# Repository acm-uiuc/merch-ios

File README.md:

# Merch Point of Sale iOS App

## Getting involved

We encourage you to participate in this open source project. We love Pull Requests, ideas, code reviews or any kind of positive contribution. GitHub issues are enabled on this repository, if you spot a bug please create a new issue.

Don't know where to start? Check issues for bugs we haven't gotten around to squashing, features we still need to implement and more. The team is active on *Gitter* and we would love to answer any questions you have.

## Requirements

XCode 8

iOS 10.2 SDK

An iPad running iOS 10.0 or newer

A Groot Client Key (more on this in API)

A code signing key from Apple is required to deploy apps to a device. Without a developer key, the app can only be installed on the iPhone/iPad Simulator.

## API

The project runs on ACM@UIUC Groot services, with routes specific to Merch maintained in https://github.com/acm-uiuc/groot-merch-service.

In order to access these services you will need a client key, which you can ask for on the Groot Gitter.

## License

This project is licensed under the University of Illinois/NCSA Open Source License. For a full copy of this license take a look at the LICENSE file. 

When contributing new files to this project, preappend the following header to the file as a comment: 

```
Copyright © 2017, ACM@UIUC

This file is part of the Merch Project.  
 
The Merch Project is open source software, released under the University of Illinois/NCSA Open Source License. 
You should have received a copy of this license in a file with the distribution.
```

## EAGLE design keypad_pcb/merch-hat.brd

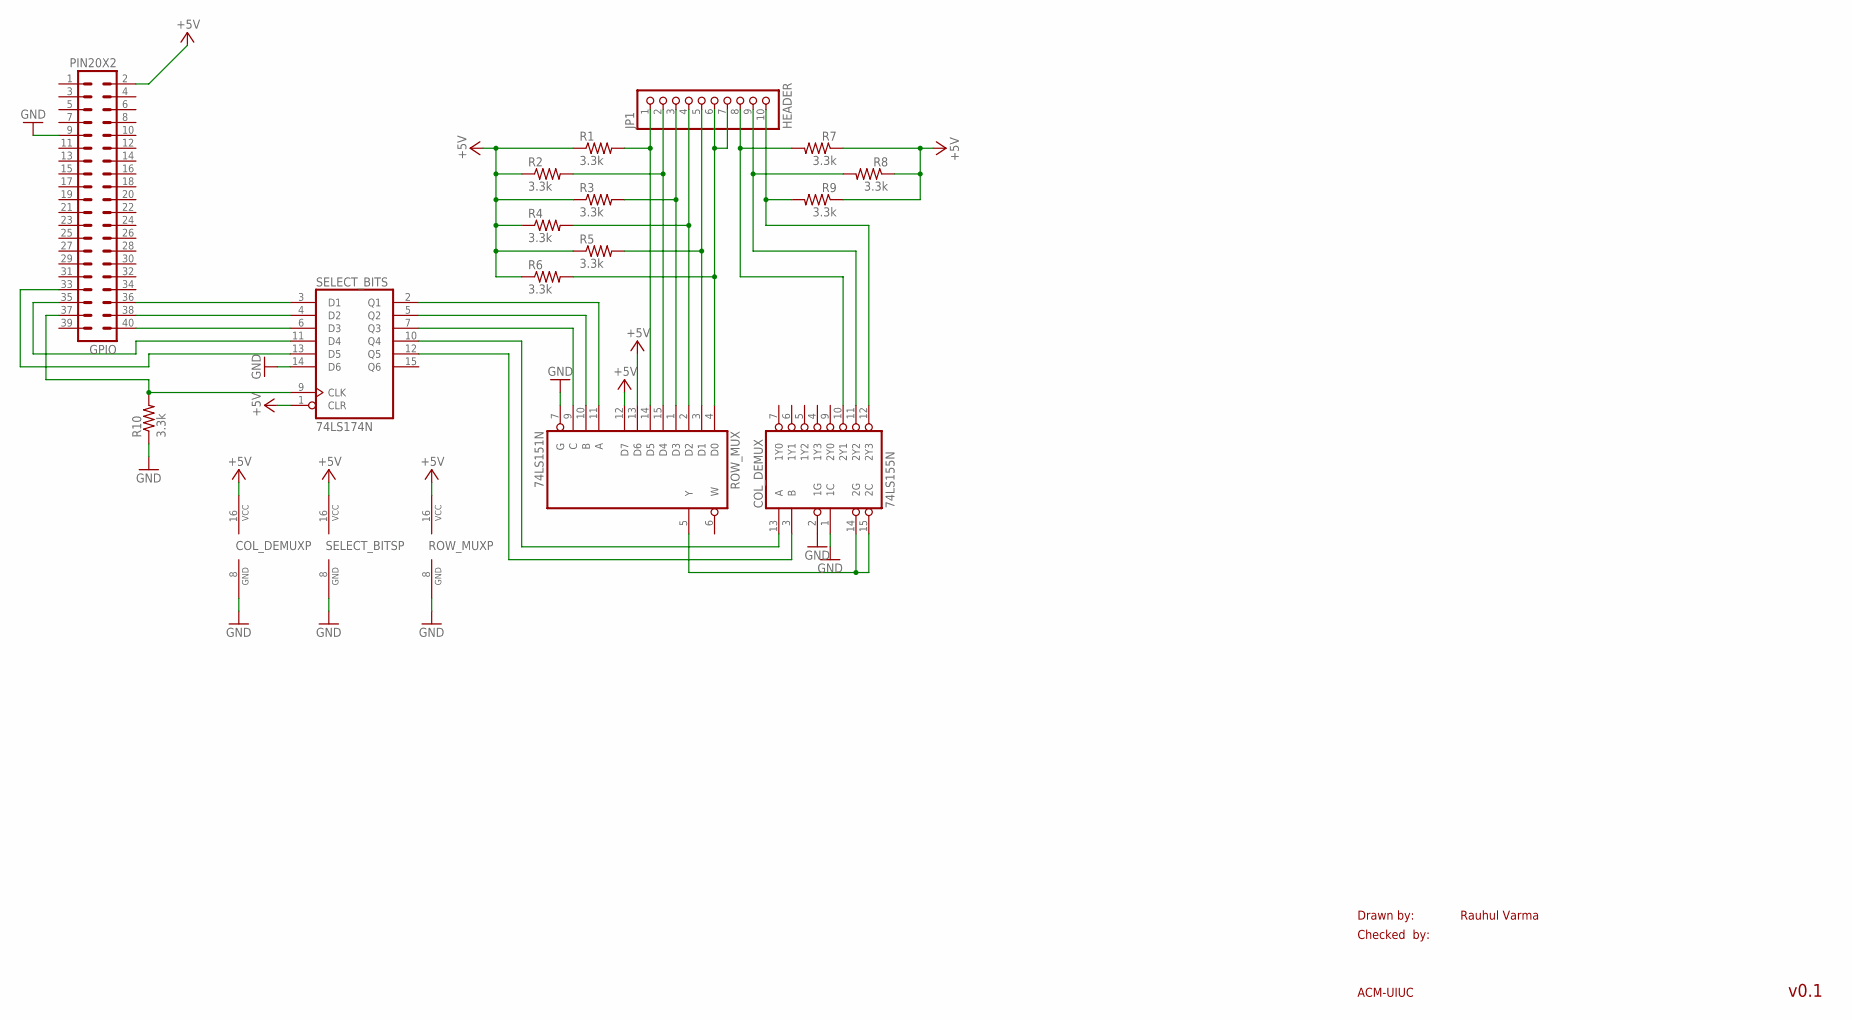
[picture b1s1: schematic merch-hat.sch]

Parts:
COL_DEMUX: 74LS155N; DIL16
GPIO: PIN20X2; PIN_20X2
JP1: HEADER; 1X10
R1, R2, R3, R4, R5, R6, R7, R8, R9, R10: 3.3k; 0207/10
ROW_MUX: 74LS151N; DIL16
SELECT_BITS: 74LS174N; DIL16

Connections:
+5V: COL_DEMUX.16 (VCC), GPIO.2, R1.1, R2.1, R3.1, R4.1, R5.1, R6.1, R7.1, R8.1, R9.1, ROW_MUX.12 (D7), ROW_MUX.13 (D6), ROW_MUX.16 (VCC), SELECT_BITS.1 (CLR), SELECT_BITS.16 (VCC)
GND: COL_DEMUX.1 (1C), COL_DEMUX.2 (1G), COL_DEMUX.8 (GND), GPIO.9, R10.1, ROW_MUX.7 (G), ROW_MUX.8 (GND), SELECT_BITS.8 (GND), SELECT_BITS.14 (D6)
unnamed: JP1.1, R1.2, ROW_MUX.14 (D5)
unnamed: GPIO.38, SELECT_BITS.4 (D2)
unnamed: GPIO.40, SELECT_BITS.6 (D3)
unnamed: JP1.2, R2.2, ROW_MUX.15 (D4)
unnamed: GPIO.35, SELECT_BITS.11 (D4)
unnamed: GPIO.36, SELECT_BITS.3 (D1)
unnamed: GPIO.33, SELECT_BITS.13 (D5)
unnamed: GPIO.37, R10.2, SELECT_BITS.9 (CLK)
unnamed: JP1.3, R3.2, ROW_MUX.1 (D3)
unnamed: JP1.4, R4.2, ROW_MUX.2 (D2)
unnamed: JP1.5, R5.2, ROW_MUX.3 (D1)
unnamed: ROW_MUX.11 (A), SELECT_BITS.2 (Q1)
unnamed: JP1.6, JP1.7, R6.2, ROW_MUX.4 (D0)
unnamed: COL_DEMUX.10 (2Y1), JP1.8, R7.2
unnamed: COL_DEMUX.11 (2Y2), JP1.9, R8.2
unnamed: COL_DEMUX.12 (2Y3), JP1.10, R9.2
unnamed: ROW_MUX.10 (B), SELECT_BITS.5 (Q2)
unnamed: ROW_MUX.9 (C), SELECT_BITS.7 (Q3)
unnamed: COL_DEMUX.13 (A), SELECT_BITS.10 (Q4)
unnamed: COL_DEMUX.3 (B), SELECT_BITS.12 (Q5)
unnamed: COL_DEMUX.14 (2G), COL_DEMUX.15 (2C), ROW_MUX.5 (Y)

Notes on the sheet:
Drawn by:
Checked by:
ACM-UIUC
Rauhul Varma
v0.1

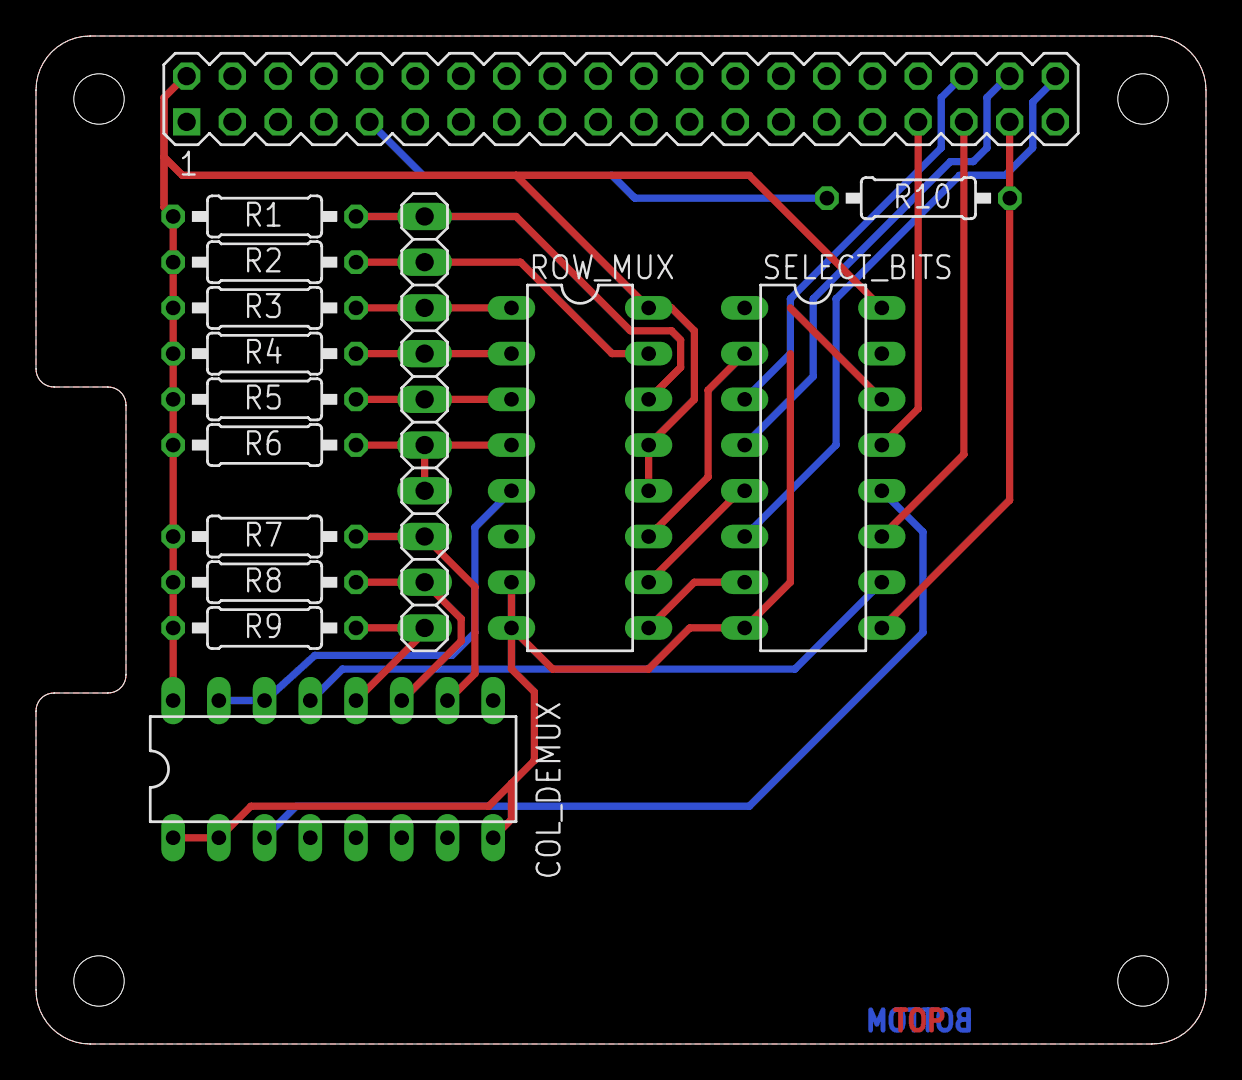
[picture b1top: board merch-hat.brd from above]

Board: 2 copper layers, 65.0 x 56.0 mm, 15 parts (0 on the bottom side), 23 nets.

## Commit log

2016-12-02 Possible documentation
2017-01-29 lcd emu does not work
2017-02-02 Fixed display reading
    Still doesn't implement all of the commands
2017-02-03 Work on rewriting state machine
    Working on a new state machine that is easier to add states to
2017-02-10 More states
2017-02-15 cursor_on, cursor_off
2017-02-17 horizonal speed, invertOff, invertOn hopefully done
2017-02-17 Merge
2017-02-17 some stuff updated
2017-02-18 Add python controller for vending through gpio
2017-02-24 add .gitignore
2017-02-24 merch components
2017-02-24 Moved some silkscreen, fixed DRU issue
2017-02-24 Add isolation and cam job
2017-02-27 initial surface mount design
2017-02-27 board images
2017-03-03 Add a timeout to the character receive to handle RESET's within a recv
2017-03-07 add iPad mount 3d models
2017-03-07 structure repo
2017-03-09 remove cocoa pod
2017-03-10 Add flask app that vends items
2017-03-18 update for PCB
2017-03-18 update pcbs to remove clear bug on 74174 chip
2017-03-18 remove eagle backupfiles
2017-03-19 finish lock screen UI
2017-03-19 Secret client key
2017-03-19 Secret client key 2
2017-03-20 Start API interaction, restructure files, migrate to offical design
2017-03-21 Completed initial login screen UI
2017-03-22 Base of ItemsViewController
2017-03-22 commit before integrating SwiftyJson via SwiftPackageManager
2017-03-22 revert point
2017-03-22 Basic API Interaction
2017-03-22 Add License
2017-03-22 only ios
2017-03-22 Readme update, incomplete
2017-03-25 Move items list into its own view controller
2017-03-26 Finish ItemsVC UI Components
2017-03-28 Increase Keypad Button Hitbox Remove secret key
2017-04-05 update gitignore
2017-04-05 Use Pods
2017-04-22 remove GrootSwift dependency
2017-04-25 Move from APIManger to GrootSwift
2017-09-03 Update LICENSE
